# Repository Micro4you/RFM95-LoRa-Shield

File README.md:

# RFM95 LoRa Shield V0.2

ดาวน์โหลด คู่มือการเชื่อมต่อเข้าระบบ LoRa IoT by CAT ฉบับ Official ได้จาก https://drive.google.com/file/d/1OALHqggIONH6ys-gYKr0pkf06lvrriyg/view

// Pin mapping

const lmic_pinmap lmic_pins = {

  .nss = 10,
  
  .rxtx = LMIC_UNUSED_PIN,
  
  .rst = 9,
  
  .dio = {2, 6, 7},
  
 ** AS923-upper (923.2-924.6MHz) LMIC-arduino code https://github.com/promwungkwa/LMIC-Arduino-AS923-upper

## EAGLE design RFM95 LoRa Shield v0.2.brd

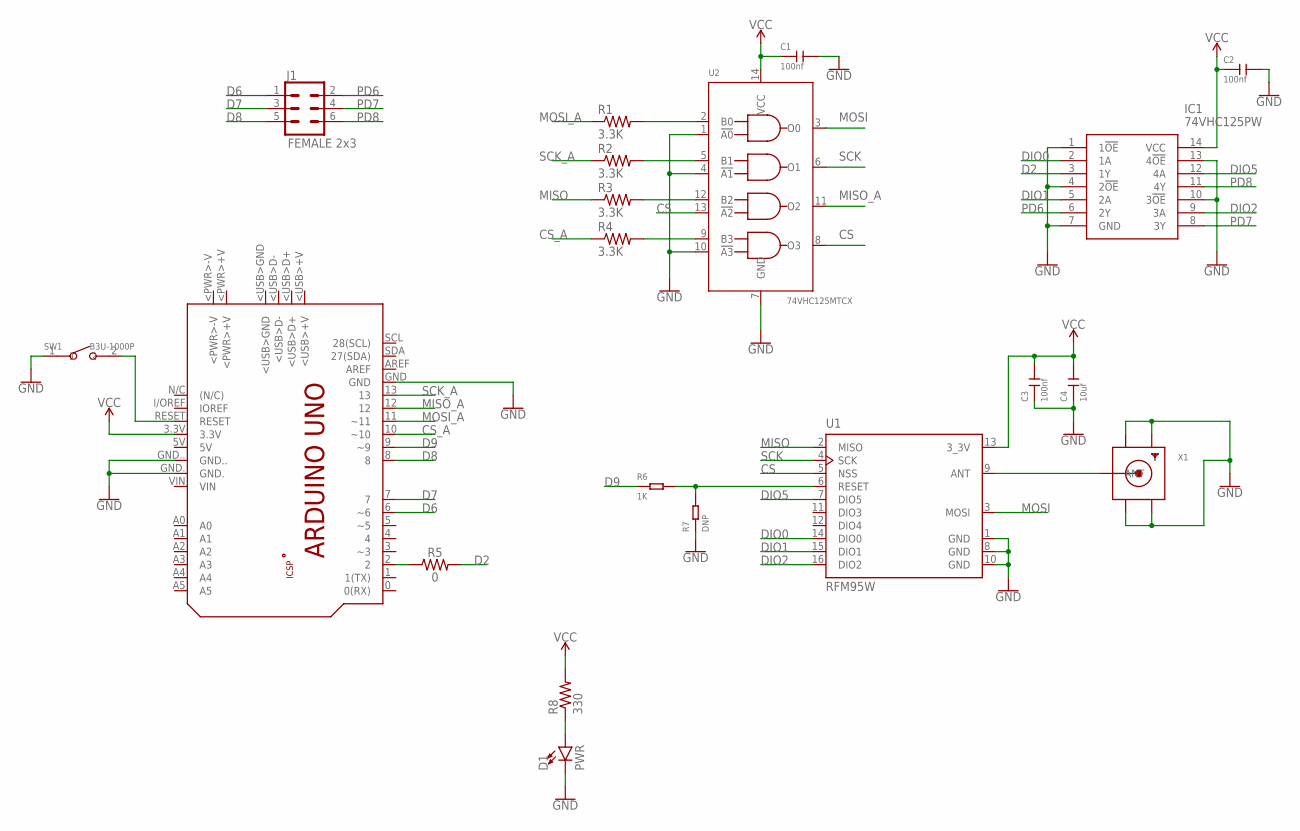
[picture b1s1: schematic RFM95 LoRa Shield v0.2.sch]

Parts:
C1, C2, C3: 100nf; C0805
C4: 10uf; C0805
D1: PWR; LED-1206
IC1: 74VHC125PW; SOP65P640X110-14N
J1: FEMALE 2x3; 2X3
PCB1: Arduino Uno; ARDUINO_UNO
R1, R2, R3, R4: 3.3K; M0805
R5: 0; 0603
R6: 1K; R0805
R7: DNP; R0805
R8: 330; M0805
SW1: B3U-1000P; SW2-2.6-3.0X2.5X1.2+0.4MM
U1: RFM95W; XCVR_RFM95W-868S2
U2: 74VHC125MTCX; TSSOP14-0.65-5X4.4MM
X1: SMACONNECTOR; SMA90_DIP

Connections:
CS: U1.5 (NSS), U2.8 (O3), U2.13 (!A2)
CS_A: PCB1.10 (~10), R4.1
D2: IC1.3 (1Y), R5.2
D6: J1.1, PCB1.6 (~6)
D7: J1.3, PCB1.7
D8: J1.5, PCB1.8
D9: PCB1.9 (~9), R6.1
DIO0: IC1.2 (1A), U1.14 (DIO0)
DIO1: IC1.5 (2A), U1.15 (DIO1)
DIO2: IC1.9 (3A), U1.16 (DIO2)
DIO5: IC1.12 (4A), U1.7 (DIO5)
GND: C1.2, C2.2, C3.1, C4.1, D1.C, IC1.1 (1!OE), IC1.4 (2!OE), IC1.7 (GND), IC1.10 (3!OE), IC1.13 (4!OE), PCB1.GND, PCB1.GND., PCB1.GND.., R7.1, SW1.1, U1.1 (GND), U1.8 (GND), U1.10 (GND), U2.1 (!A0), U2.4 (!A1), U2.7 (GND), U2.10 (!A3), X1.GND1, X1.GND2, X1.GND3, X1.GND4
MISO: R3.1, U1.2 (MISO)
MISO_A: PCB1.12, U2.11 (O2)
MOSI: U1.3 (MOSI), U2.3 (O0)
MOSI_A: PCB1.11 (~11), R1.1
unnamed: R1.2, U2.2 (B0)
unnamed: R2.2, U2.5 (B1)
unnamed: R3.2, U2.12 (B2)
unnamed: R4.2, U2.9 (B3)
unnamed: PCB1.2, R5.1
unnamed: R6.2, R7.2, U1.6 (RESET)
unnamed: U1.9 (ANT), X1.ANTENNA (ANT)
unnamed: PCB1.RESET, SW1.2
unnamed: D1.A, R8.1
PD6: IC1.6 (2Y), J1.2
PD7: IC1.8 (3Y), J1.4
PD8: IC1.11 (4Y), J1.6
SCK: U1.4 (SCK), U2.6 (O1)
SCK_A: PCB1.13, R2.1
VCC: C1.1, C2.1, C3.2, C4.2, IC1.14 (VCC), PCB1.3.3V, R8.2, U1.13 (3_3V), U2.14 (VCC)

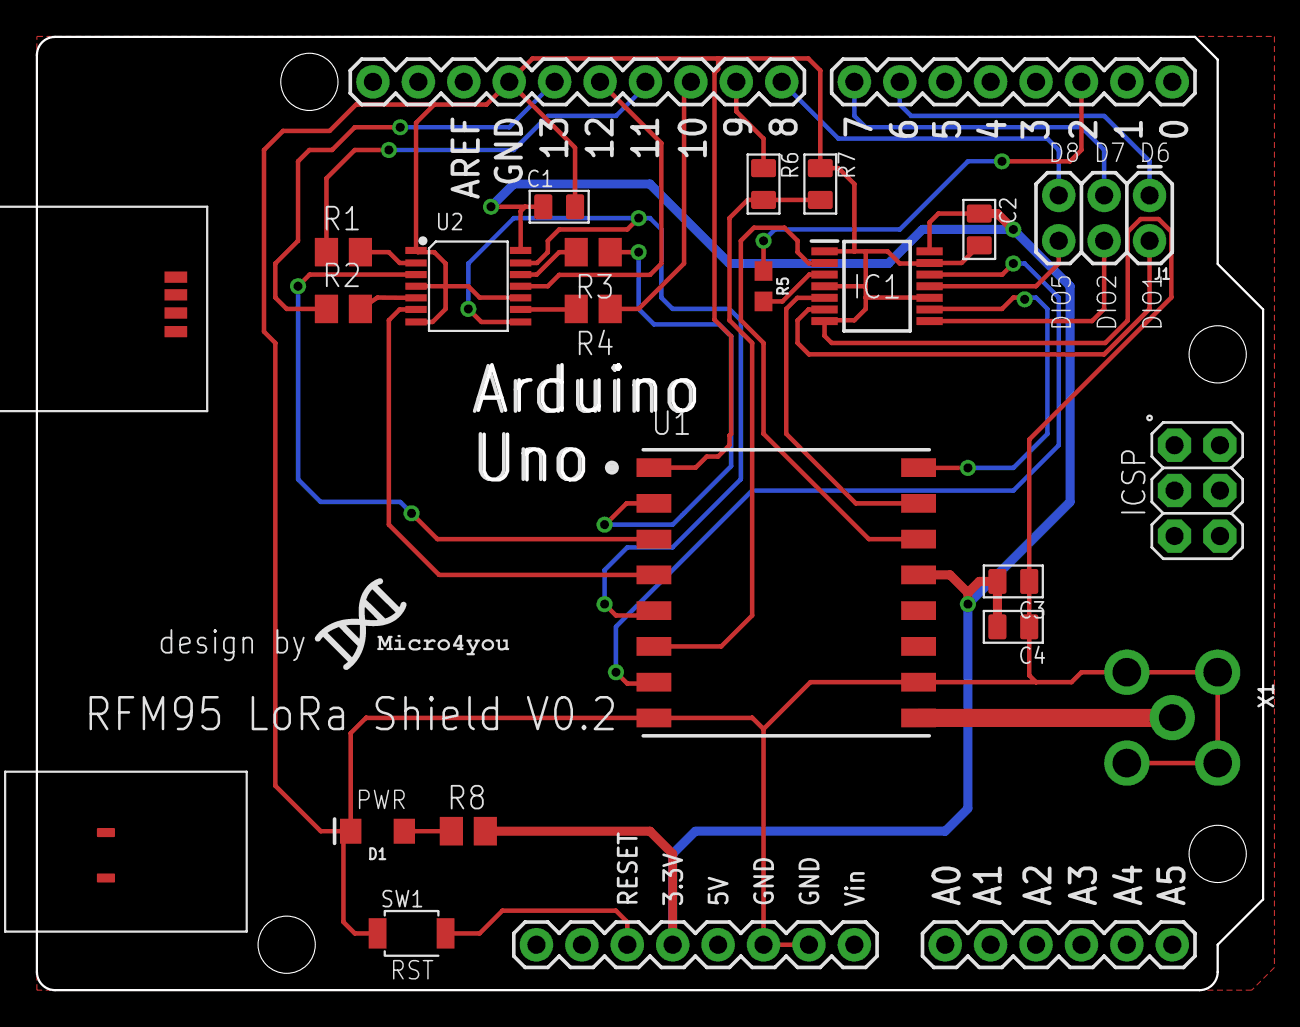
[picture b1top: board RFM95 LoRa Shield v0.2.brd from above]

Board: 2 copper layers, 68.6 x 53.3 mm, 20 parts (0 on the bottom side), 31 nets.

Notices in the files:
parts and their libraries:
SparkFun-Connectors: Licensing: Creative Commons ShareAlike 4.0 International - https://creativecommons.org/licenses/by-sa/4.0
